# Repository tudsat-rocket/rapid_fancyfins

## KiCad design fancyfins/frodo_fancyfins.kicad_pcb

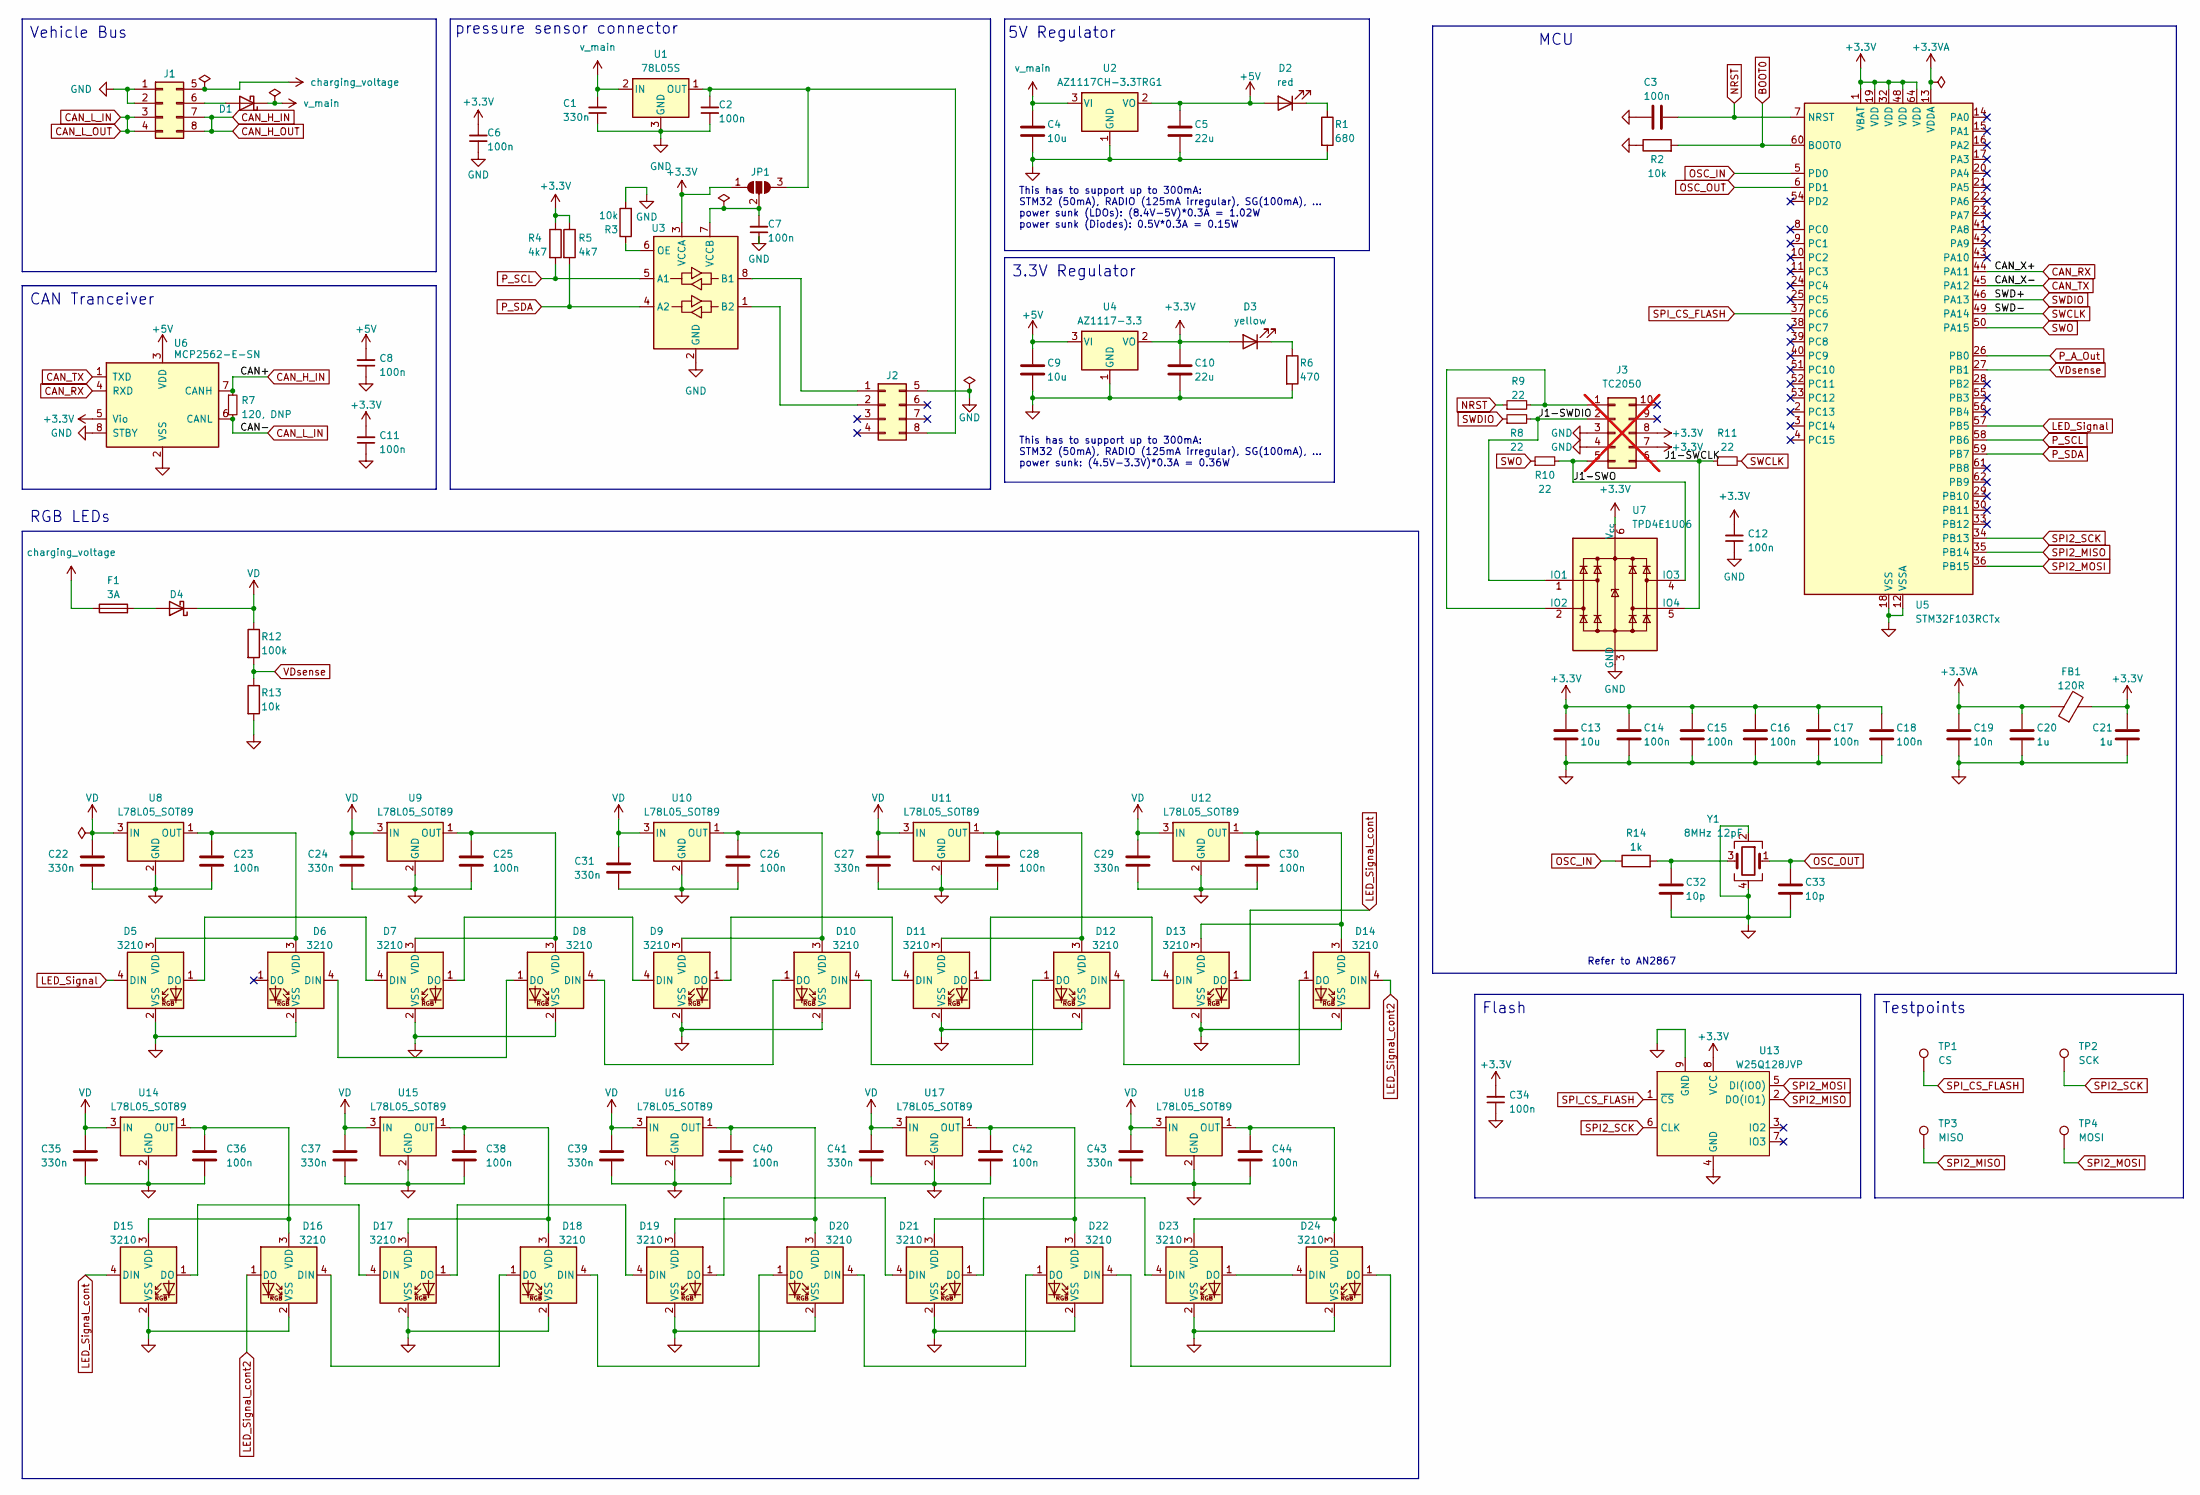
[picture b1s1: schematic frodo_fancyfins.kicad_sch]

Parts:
C1: 330n; C_0402_1005Metric
C2, C6, C7, C12: 100n; C_0402_1005Metric; Part# CL10B104KB8NNNC; LCSC C1525
C3, C8, C11, C14, C15, C16, C17, C18, C34: 100n; C_0402_1005Metric_Pad0.74x0.62mm_HandSolder; LCSC# C307331
C4, C9, C13: 10u; C_0603_1608Metric_Pad1.08x0.95mm_HandSolder; LCSC# C96446
C5, C10: 22u; C_0805_2012Metric_Pad1.18x1.45mm_HandSolder; LCSC# C45783
C19: 10n; C_0402_1005Metric; LCSC# C15195
C20, C21: 1u; C_0402_1005Metric; LCSC# C14445
C22, C24, C27, C29, C31, C35, C37, C39, C41, C43: 330n; C_0402_1005Metric; LCSC# C5448882
C23, C25, C26, C28, C30, C36, C38, C40, C42, C44: 100n; C_0402_1005Metric; LCSC# C1525
C32, C33: 10p; C_0402_1005Metric_Pad0.74x0.62mm_HandSolder; LCSC# C32949
D1: SK34; D_SMA; LCSC # C5140034
D2: red; LED_0603_1608Metric_Pad1.05x0.95mm_HandSolder; LCSC# C2286
D3: yellow; LED_0603_1608Metric_Pad1.05x0.95mm_HandSolder; LCSC# C72038
D4: SK34; D_SMA; LCSC# C5140034
D5, D6, D7, D8, D9, D10, D11, D12, D13, D14, D15, D16, D17, D18, D19, D20, D21, D22, D23, D24: 3210; 1313210530000
F1: 3A; Fuse_1206_3216Metric_Pad1.42x1.75mm_HandSolder
FB1: 120R; L_0402_1005Metric; LCSC# C1002
J1, J2: card_edge_connector_2x4
J3: TC2050; Tag-Connect_TC2050-IDC-FP_2x05_P1.27mm_Vertical; not fitted
JP1: SolderJumper_3_Open; SolderJumper-3_P1.3mm_Open_RoundedPad1.0x1.5mm
R1: 680; R_0603_1608Metric_Pad0.98x0.95mm_HandSolder; LCSC# C23228
R2, R3, R13: 10k; R_0402_1005Metric; LCSC# C25744
R4, R5: 4k7; R_0603_1608Metric
R6: 470; R_0402_1005Metric; LCSC# C25117
R7: 120, DNP; R_0603_1608Metric_Pad0.98x0.95mm_HandSolder
R8, R9, R10, R11: 22; R_0402_1005Metric; Part# RC0603FR-0710KL; LCSC C25092
R12: 100k; R_0402_1005Metric; LCSC# C25741
R14: 1k; R_0402_1005Metric; LCSC# C11702
TP1: CS; TestPoint_Pad_D2.0mm
TP2: SCK; TestPoint_Pad_D2.0mm
TP3: MISO; TestPoint_Pad_D2.0mm
TP4: MOSI; TestPoint_Pad_D2.0mm
U1: 78L05S; SOT-23; LCSC# C2983743
U2: AZ1117CH-3.3TRG1; SOT-223-3_TabPin2; LCSC# C92102
U3: TXB0102DCU; VSSOP-8_2.3x2mm_P0.5mm
U4: AZ1117-3.3; SOT-223-3_TabPin2; LCSC# C110474
U5: STM32F103RCTx; LQFP-64_10x10mm_P0.5mm; LCSC# C8323
U6: MCP2562-E-SN; SOIC-8_3.9x4.9mm_P1.27mm; DigiKey# MCP2562-H/SN
U7: TPD4E1U06; SOT-563; LCSC C527516
U8, U9, U10, U11, U12, U14, U15, U16, U17, U18: L78L05_SOT89; SOT-89-3; LCSC# C42738
U13: W25Q128JVP; WSON-8-1EP_6x5mm_P1.27mm_EP3.4x4.3mm; LCSC# C190862
Y1: 8MHz 12pF; Crystal_SMD_5032-4Pin_5.0x3.2mm; LCSC# C2149245

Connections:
+3.3V: C6.2, C10.1, C11.2, C12.2, C13.1, C14.1, C15.1, C16.1, C17.1, C18.1, C21.1, C34.2, D3.2 (A), FB1.2, J3.7, J3.8, JP1.1 (A), R4.1, R5.1, U3.3 (VCCA), U4.2 (VO), U5.1 (VBAT), U5.19 (VDD), U5.32 (VDD), U5.48 (VDD), U5.64 (VDD), U6.5 (Vio), U7.6 (V_{cc}), U13.8 (VCC)
+3.3VA: C19.1, C20.1, FB1.1, U5.13 (VDDA)
+5V: C5.1, C8.2, C9.1, D2.2 (A), U2.2 (VO), U4.3 (VI), U6.3 (VDD)
/J1-SWCLK: J3.6, R11.1, U7.5 (IO4)
/J1-SWDIO: J3.2, R8.2, U7.1 (IO1)
/J1-SWO: J3.5, R10.2, U7.4 (IO3)
BOOT0: R2.2, U5.60 (BOOT0)
CAN_H_IN: J1.7, J1.8, R7.1, U6.7 (CANH)
CAN_L_IN: J1.3, J1.4, R7.2, U6.6 (CANL)
CAN_RX: U5.44 (PA11), U6.4 (RXD)
CAN_TX: U5.45 (PA12), U6.1 (TXD)
GND: C1.1, C2.1, C3.2, C4.2, C5.2, C6.1, C7.1, C8.1, C9.2, C10.2, C11.1, C12.1, C13.2, C14.2, C15.2, C16.2, C17.2, C18.2, C19.2, C20.2, C21.2, C22.2, C23.2, C24.2, C25.2, C26.2, C27.2, C28.2, C29.2, C30.2, C31.2, C32.2, C33.2, C34.1, C35.2, C36.2, C37.2, C38.2, C39.2, C40.2, C41.2, C42.2, C43.2, C44.2, D5.2 (VSS), D6.2 (VSS), D7.2 (VSS), D8.2 (VSS), D9.2 (VSS), D10.2 (VSS), D11.2 (VSS), D12.2 (VSS), D13.2 (VSS), D14.2 (VSS), D15.2 (VSS), D16.2 (VSS), D17.2 (VSS), D18.2 (VSS), D19.2 (VSS), D20.2 (VSS), D21.2 (VSS), D22.2 (VSS), D23.2 (VSS), D24.2 (VSS), J1.1, J1.2, J2.5, J3.3, J3.4, R1.2, R2.1, R3.2, R6.2, R13.2, U1.3 (GND), U2.1 (GND), U3.2 (GND), U4.1 (GND), U5.12 (VSSA), U5.18 (VSS), U5.31 (VSS), U5.47 (VSS), U5.63 (VSS), U6.2 (VSS), U6.8 (STBY), U7.3 (GND), U8.2 (GND), U9.2 (GND), U10.2 (GND), U11.2 (GND), U12.2 (GND), U13.4 (GND), U13.9 (GND), U14.2 (GND), U15.2 (GND), U16.2 (GND), U17.2 (GND), U18.2 (GND), Y1.2, Y1.4
LED_Signal: D5.4 (DIN), U5.57 (PB5)
LED_Signal_cont: D13.1 (DO), D15.4 (DIN)
LED_Signal_cont2: D14.4 (DIN), D16.1 (DO)
NRST: C3.1, R9.1, U5.7 (NRST)
unnamed: C32.1, R14.2, Y1.3
unnamed: D1.2 (A), J1.6
unnamed: D2.1 (K), R1.1
unnamed: D3.1 (K), R6.1
unnamed: D4.2 (A), F1.2
unnamed: D5.1 (DO), D7.4 (DIN)
unnamed: C23.1, D5.3 (VDD), D6.3 (VDD), U8.1 (OUT)
unnamed: D6.4 (DIN), D8.1 (DO)
unnamed: D7.1 (DO), D9.4 (DIN)
unnamed: C25.1, D7.3 (VDD), D8.3 (VDD), U9.1 (OUT)
unnamed: D10.4 (DIN), D12.1 (DO)
unnamed: D8.4 (DIN), D10.1 (DO)
unnamed: C26.1, D9.3 (VDD), D10.3 (VDD), U10.1 (OUT)
unnamed: D9.1 (DO), D11.4 (DIN)
unnamed: D11.1 (DO), D13.4 (DIN)
unnamed: C28.1, D11.3 (VDD), D12.3 (VDD), U11.1 (OUT)
unnamed: D12.4 (DIN), D14.1 (DO)
unnamed: C30.1, D13.3 (VDD), D14.3 (VDD), U12.1 (OUT)
unnamed: D15.1 (DO), D17.4 (DIN)
unnamed: C36.1, D15.3 (VDD), D16.3 (VDD), U14.1 (OUT)
unnamed: D16.4 (DIN), D18.1 (DO)
unnamed: D17.1 (DO), D19.4 (DIN)
unnamed: C38.1, D17.3 (VDD), D18.3 (VDD), U15.1 (OUT)
unnamed: D18.4 (DIN), D20.1 (DO)
unnamed: D19.1 (DO), D21.4 (DIN)
unnamed: C40.1, D19.3 (VDD), D20.3 (VDD), U16.1 (OUT)
unnamed: D20.4 (DIN), D22.1 (DO)
unnamed: D21.1 (DO), D23.4 (DIN)
unnamed: C42.1, D21.3 (VDD), D22.3 (VDD), U17.1 (OUT)
unnamed: D22.4 (DIN), D24.1 (DO)
unnamed: D23.1 (DO), D24.4 (DIN)
unnamed: C44.1, D23.3 (VDD), D24.3 (VDD), U18.1 (OUT)
unnamed: J2.1, U3.8 (B1)
unnamed: J2.2, U3.1 (B2)
unnamed: C2.2, J2.8, JP1.3 (B), U1.1 (OUT)
unnamed: J3.1, R9.2, U7.2 (IO2)
unnamed: C7.2, JP1.2 (C), U3.7 (VCCB)
unnamed: R3.1, U3.6 (OE)
OSC_IN: R14.1, U5.5 (PD0)
OSC_OUT: C33.1, U5.6 (PD1), Y1.1
P_A_Out: U5.26 (PB0)
P_SCL: R4.2, U3.5 (A1), U5.58 (PB6)
P_SDA: R5.2, U3.4 (A2), U5.59 (PB7)
SPI2_MISO: TP3.1, U5.35 (PB14), U13.2 (DO(IO1))
SPI2_MOSI: TP4.1, U5.36 (PB15), U13.5 (DI(IO0))
SPI2_SCK: TP2.1, U5.34 (PB13), U13.6 (CLK)
SPI_CS_FLASH: TP1.1, U5.37 (PC6), U13.1 (~CS)
SWCLK: R11.2, U5.49 (PA14)
SWDIO: R8.1, U5.46 (PA13)
SWO: R10.1, U5.50 (PA15)
VD: C22.1, C24.1, C27.1, C29.1, C31.1, C35.1, C37.1, C39.1, C41.1, C43.1, D4.1 (K), R12.1, U8.3 (IN), U9.3 (IN), U10.3 (IN), U11.3 (IN), U12.3 (IN), U14.3 (IN), U15.3 (IN), U16.3 (IN), U17.3 (IN), U18.3 (IN)
VDsense: R12.2, R13.1, U5.27 (PB1)
charging_voltage: F1.1, J1.5
v_main: C1.2, C4.1, D1.1 (K), U1.2 (IN), U2.3 (VI)

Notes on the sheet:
This has to support up to 300mA: STM32 (50mA), RADIO (125mA irregular), SG(100mA), ... power sunk (LDOs): (8.4V-5V)*0.3A = 1.02W power sunk (Diodes): 0.5V*0.3A = 0.15W
Vehicle Bus
CAN Tranceiver
Flash
Refer to AN2867
5V Regulator
This has to support up to 300mA: STM32 (50mA), RADIO (125mA irregular), SG(100mA), ... power sunk: (4.5V-3.3V)*0.3A = 0.36W
3.3V Regulator
Testpoints
RGB LEDs
pressure sensor connector
MCU

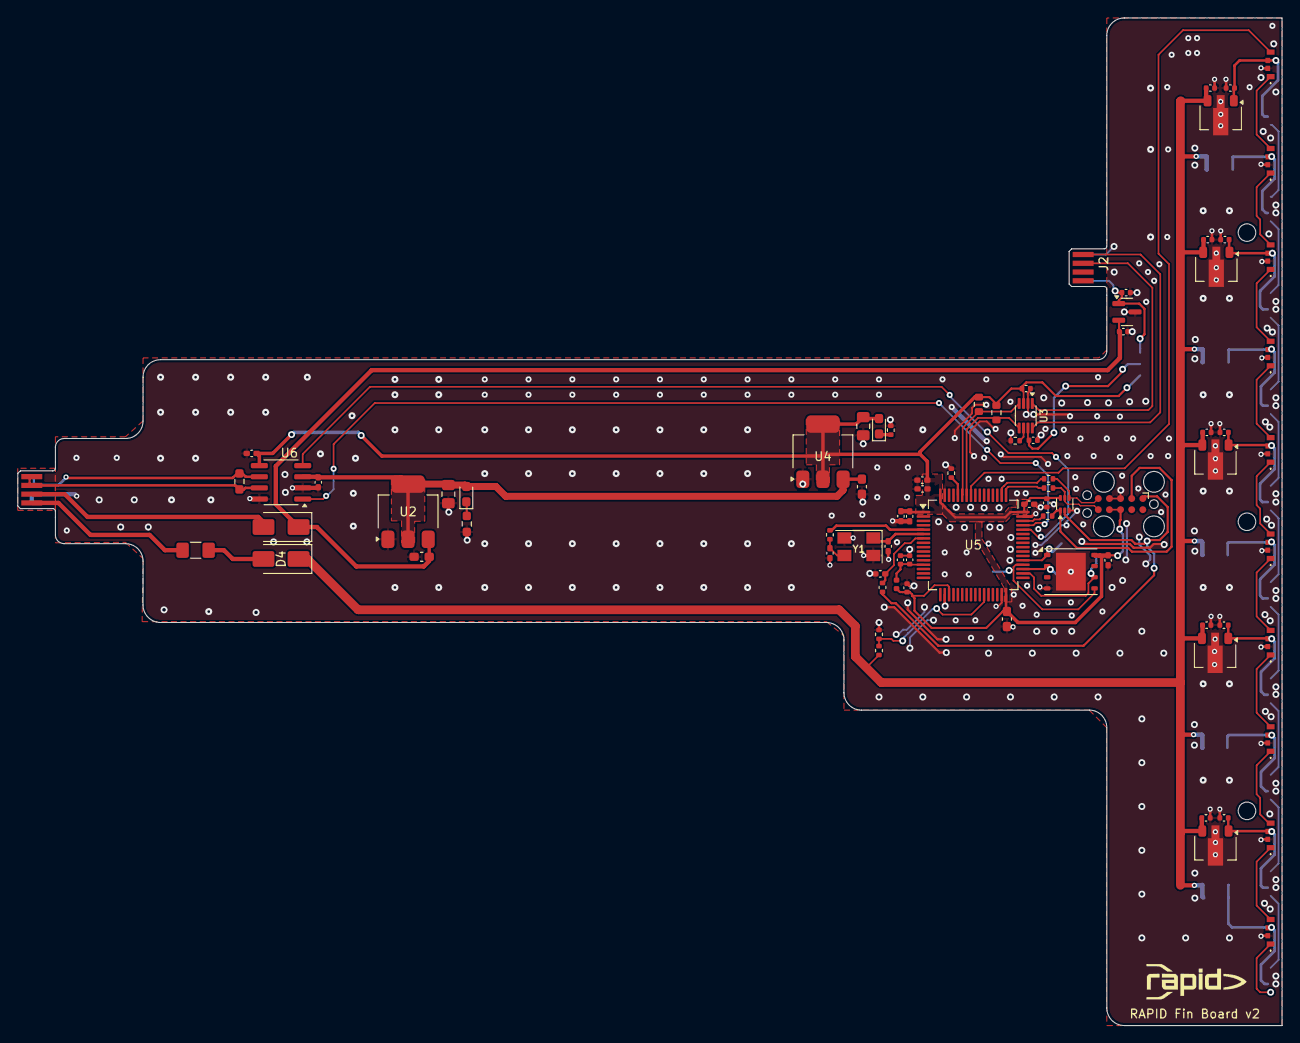
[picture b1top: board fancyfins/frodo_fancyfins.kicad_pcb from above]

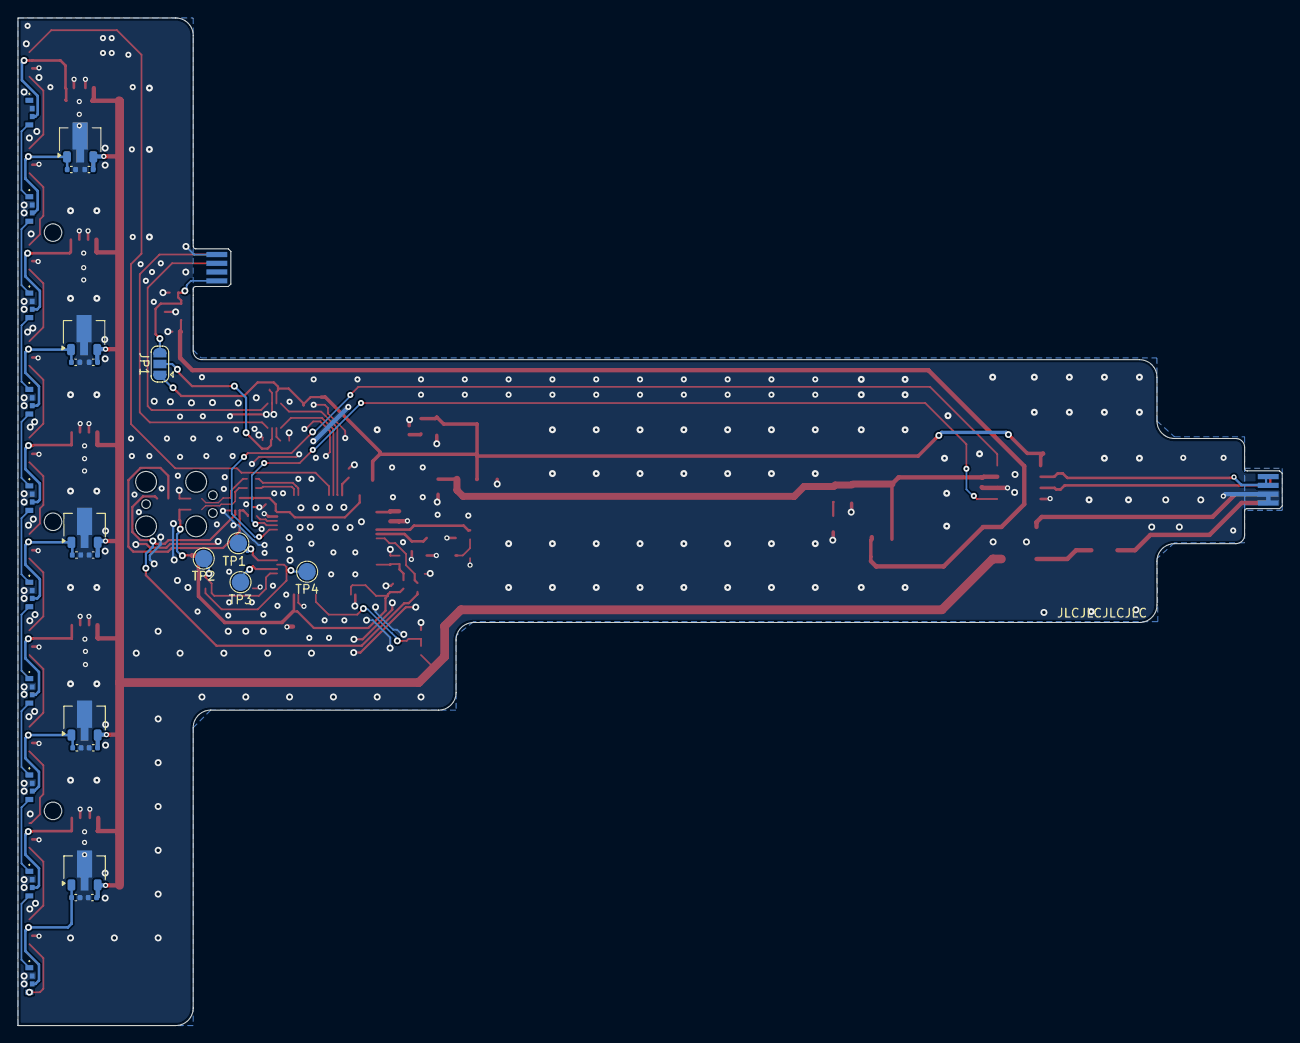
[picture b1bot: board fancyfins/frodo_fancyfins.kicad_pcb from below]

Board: 2 copper layers, 144.3 x 115.0 mm, 111 parts (31 on the bottom side), 69 nets.

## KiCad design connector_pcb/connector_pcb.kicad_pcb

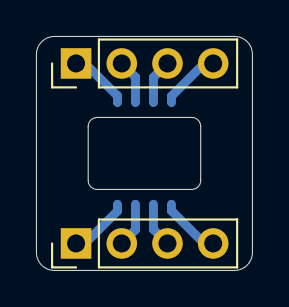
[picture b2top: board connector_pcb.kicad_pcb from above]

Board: 2 copper layers, 12.0 x 13.0 mm, 3 parts (1 on the bottom side), 8 nets.

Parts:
J1: Conn_01x04_Pin; PinHeader_1x04_P2.54mm_Vertical
J2: PinHeader_1x04_P2.54mm_Vertical
J7: Conn_02x04_Top_Bottom; 009159008801906

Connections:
unnamed: J1.1, J7.1
unnamed: J1.2, J7.2
unnamed: J1.3, J7.3
unnamed: J1.4, J7.4
unnamed: J2.1, J7.5
unnamed: J2.2, J7.6
unnamed: J2.3, J7.7
unnamed: J2.4, J7.8

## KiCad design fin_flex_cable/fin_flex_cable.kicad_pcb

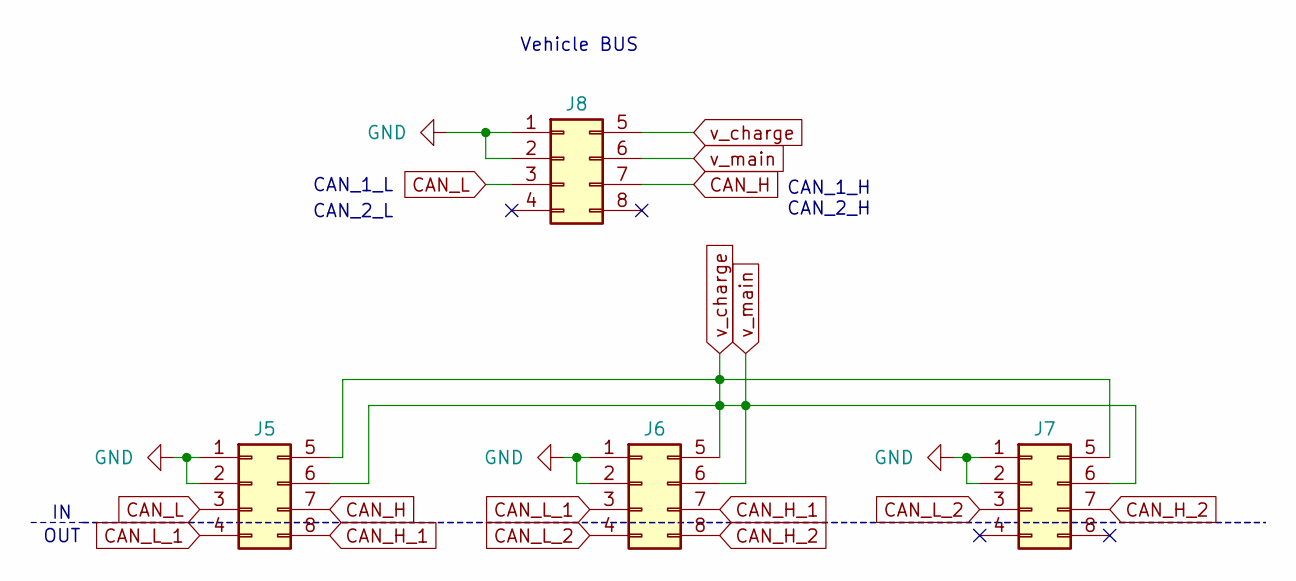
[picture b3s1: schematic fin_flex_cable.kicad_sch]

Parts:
J5, J6, J7: Conn_02x04_Top_Bottom; 009159008801906; Mouser-Nr.: 581-009159008801906
J8: Molex_Micro-Fit_3.0_43045-0800_2x04_P3.00mm_Horizontal

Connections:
CAN_H: J5.7, J8.7
CAN_H_1: J5.8, J6.7
CAN_H_2: J6.8, J7.7
CAN_L: J5.3, J8.3
CAN_L_1: J5.4, J6.3
CAN_L_2: J6.4, J7.3
GND: J5.1, J5.2, J6.1, J6.2, J7.1, J7.2, J8.1, J8.2
v_charge: J5.5, J5.6, J6.5, J6.6, J7.5, J7.6, J8.5, J8.6

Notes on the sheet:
OUT
Vehicle BUS
CAN_1_L
CAN_2_H
CAN_2_L
CAN_1_H

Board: 2 copper layers, 4 parts (0 on the bottom side), 8 nets, no tracks yet.

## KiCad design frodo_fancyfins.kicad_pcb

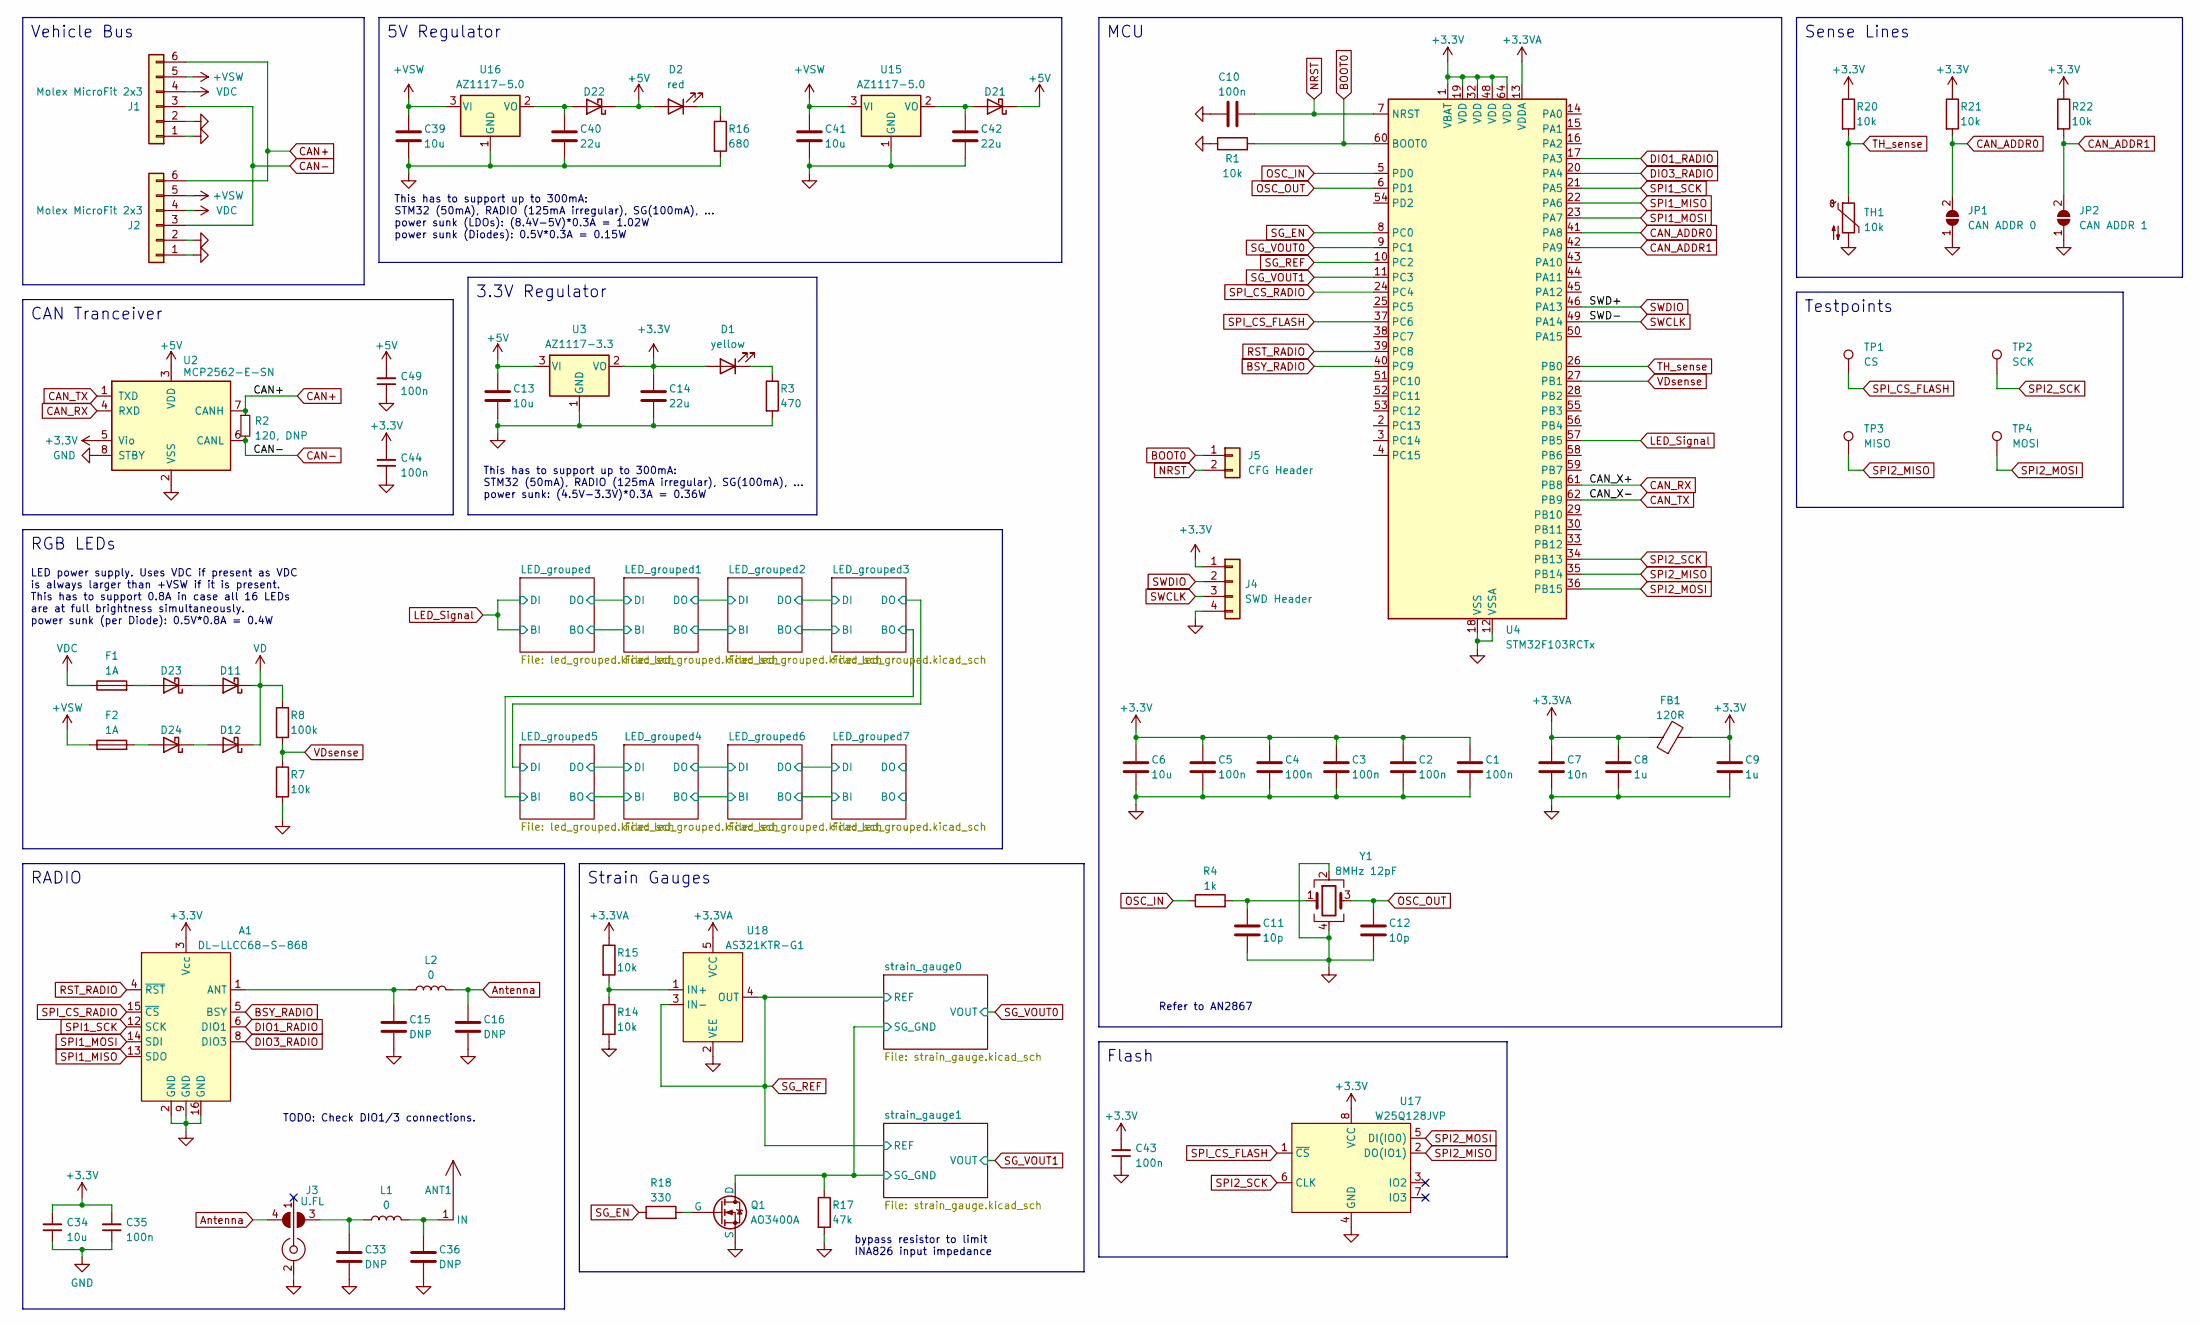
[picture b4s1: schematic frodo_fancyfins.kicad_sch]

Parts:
A1: DL-LLCC68-S-868
ANT1: meandering_monopole_antenna_868MHz
C1, C2, C3, C4, C5, C10, C35, C43, C44, C49: 100n; C_0402_1005Metric_Pad0.74x0.62mm_HandSolder; LCSC# C307331
C6, C13, C34, C39, C41: 10u; C_0603_1608Metric_Pad1.08x0.95mm_HandSolder; LCSC# C96446
C7: 10n; C_0402_1005Metric_Pad0.74x0.62mm_HandSolder; LCSC# C15195
C8, C9: 1u; C_0603_1608Metric_Pad1.08x0.95mm_HandSolder; LCSC# C15849
C11, C12: 10p; C_0402_1005Metric_Pad0.74x0.62mm_HandSolder; LCSC# C32949
C14, C40, C42: 22u; C_0805_2012Metric_Pad1.18x1.45mm_HandSolder; LCSC# C45783
C15, C16, C33, C36: DNP; C_0603_1608Metric_Pad1.08x0.95mm_HandSolder
D1: yellow; LED_0603_1608Metric_Pad1.05x0.95mm_HandSolder; LCSC# C72038
D2: red; LED_0603_1608Metric_Pad1.05x0.95mm_HandSolder; LCSC# C2286
D11, D12, D21, D22, D23, D24: D_Schottky; D_SOD-123F; LCSC# C167645
F1, F2: 1A; Fuse_1206_3216Metric_Pad1.42x1.75mm_HandSolder
FB1: 120R; L_0603_1608Metric_Pad1.05x0.95mm_HandSolder; LCSC# C1002
J1, J2: Molex MicroFit 2x3; Molex_Micro-Fit_3.0_43045-0612_2x03_P3.00mm_Vertical
J3: U.FL; SolderJumper-U.FL
J4: SWD Header; PinHeader_1x04_P2.54mm_Vertical
J5: CFG Header; PinHeader_1x02_P2.54mm_Vertical
JP1: CAN ADDR 0; SolderJumper-2_P1.3mm_Open_RoundedPad1.0x1.5mm
JP2: CAN ADDR 1; SolderJumper-2_P1.3mm_Open_RoundedPad1.0x1.5mm
L1, L2: 0; L_0603_1608Metric_Pad1.05x0.95mm_HandSolder
Q1: AO3400A; SOT-23-3; LCSC# C20917
R1, R7, R14, R15: 10k; R_0402_1005Metric_Pad0.72x0.64mm_HandSolder; LCSC# C25744
R2: 120, DNP; R_0603_1608Metric_Pad0.98x0.95mm_HandSolder
R3: 470; R_0402_1005Metric_Pad0.72x0.64mm_HandSolder; LCSC# C25117
R4: 1k; R_0402_1005Metric_Pad0.72x0.64mm_HandSolder; LCSC# C11702
R8: 100k; R_0402_1005Metric_Pad0.72x0.64mm_HandSolder; LCSC# C25741
R16: 680; R_0603_1608Metric_Pad0.98x0.95mm_HandSolder; LCSC# C23228
R17: 47k; R_0402_1005Metric_Pad0.72x0.64mm_HandSolder; LCSC# C25792
R18: 330; R_0402_1005Metric_Pad0.72x0.64mm_HandSolder; LCSC# C25104
R20, R21, R22: 10k; R_0603_1608Metric_Pad0.98x0.95mm_HandSolder; LCSC# C25804
TH1: 10k; R_0603_1608Metric_Pad0.98x0.95mm_HandSolder; Part# NCP18XH103F03RB; LCSC# C13564
TP1: CS; TestPoint_Pad_D2.0mm
TP2: SCK; TestPoint_Pad_D2.0mm
TP3: MISO; TestPoint_Pad_D2.0mm
TP4: MOSI; TestPoint_Pad_D2.0mm
U2: MCP2562-E-SN; SOIC-8_3.9x4.9mm_P1.27mm; DigiKey# MCP2562-H/SN
U3: AZ1117-3.3; SOT-223-3_TabPin2; LCSC# C110474
U4: STM32F103RCTx; LQFP-64_10x10mm_P0.5mm; LCSC# C8323
U15, U16: AZ1117-5.0; SOT-223-3_TabPin2; LCSC# C526405
U17: W25Q128JVP; WSON-8-1EP_6x5mm_P1.27mm_EP3.4x4.3mm; LCSC# C190862
U18: AS321KTR-G1; SOT25; LCSC# C144156
Y1: 8MHz 12pF; Crystal_SMD_5032-4Pin_5.0x3.2mm; LCSC# C2149245

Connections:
+5V: C13.1, C49.2, D2.2 (A), D21.1 (K), D22.1 (K), U2.3 (VDD), U3.3 (VI)
+VSW: C39.1, C41.1, F2.1, J1.5, J2.5, U15.3 (VI), U16.3 (VI)
/strain_gauge0/SG_GND: Q1.3 (D), R17.1; also elsewhere on the board
Antenna: C16.1, J3.4, L2.2
BOOT0: J5.1, R1.2, U4.60 (BOOT0)
BSY_RADIO: A1.5 (BSY), U4.40 (PC9)
CAN+: J1.6, J2.6, R2.1, U2.7 (CANH)
CAN-: J1.3, J2.3, R2.2, U2.6 (CANL)
CAN_ADDR0: JP1.2 (B), R21.2, U4.41 (PA8)
CAN_ADDR1: JP2.2 (B), R22.2, U4.42 (PA9)
CAN_RX: U2.4 (RXD), U4.61 (PB8)
CAN_TX: U2.1 (TXD), U4.62 (PB9)
DIO1_RADIO: A1.6 (DIO1), U4.17 (PA3)
DIO3_RADIO: A1.8 (DIO3), U4.20 (PA4)
GND: A1.2 (GND), A1.9 (GND), A1.16 (GND), C1.2, C2.2, C3.2, C4.2, C5.2, C6.2, C7.2, C8.2, C9.2, C10.2, C11.2, C12.2, C13.2, C14.2, C15.2, C16.2, C33.2, C34.1, C35.1, C36.2, C39.2, C40.2, C41.2, C42.2, C43.1, C44.1, C49.1, J1.1, J1.2, J2.1, J2.2, J3.2, J4.4, JP1.1 (A), JP2.1 (A), Q1.2 (S), R1.1, R3.2, R7.2, R14.2, R16.2, R17.2, TH1.2, U2.2 (VSS), U2.8 (STBY), U3.1 (GND), U4.12 (VSSA), U4.18 (VSS), U4.31 (VSS), U4.47 (VSS), U4.63 (VSS), U15.1 (GND), U16.1 (GND), U17.4 (GND), U18.2 (VEE), Y1.2, Y1.4; also elsewhere on the board
LED_Signal: U4.57 (PB5); also elsewhere on the board
NRST: C10.1, J5.2, U4.7 (NRST)
unnamed: A1.1 (ANT), C15.1, L2.1
unnamed: ANT1.1 (IN), C36.1, L1.2
unnamed: C11.1, R4.2, Y1.1
unnamed: C33.1, J3.3, L1.1
unnamed: D1.1 (K), R3.1
unnamed: D2.1 (K), R16.1
unnamed: D11.2 (A), D23.1 (K)
unnamed: D12.2 (A), D24.1 (K)
unnamed: C42.1, D21.2 (A), U15.2 (VO)
unnamed: C40.1, D22.2 (A), U16.2 (VO)
unnamed: D23.2 (A), F1.2
unnamed: D24.2 (A), F2.2
unnamed: Q1.1 (G), R18.2
unnamed: R14.1, R15.2, U18.1 (IN+)
OSC_IN: R4.1, U4.5 (PD0)
OSC_OUT: C12.1, U4.6 (PD1), Y1.3
RST_RADIO: A1.4 (~RST), U4.39 (PC8)
SG_EN: R18.1, U4.8 (PC0)
SG_REF: U4.10 (PC2), U18.3 (IN-), U18.4 (OUT); also elsewhere on the board
SG_VOUT0: U4.9 (PC1); also elsewhere on the board
SG_VOUT1: U4.11 (PC3); also elsewhere on the board
SPI1_MISO: A1.13 (SDO), U4.22 (PA6)
SPI1_MOSI: A1.14 (SDI), U4.23 (PA7)
SPI1_SCK: A1.12 (SCK), U4.21 (PA5)
SPI2_MISO: TP3.1, U4.35 (PB14), U17.2 (DO(IO1))
SPI2_MOSI: TP4.1, U4.36 (PB15), U17.5 (DI(IO0))
SPI2_SCK: TP2.1, U4.34 (PB13), U17.6 (CLK)
SPI_CS_FLASH: TP1.1, U4.37 (PC6), U17.1 (~CS)
SPI_CS_RADIO: A1.15 (~CS), U4.24 (PC4)
SWCLK: J4.3, U4.49 (PA14)
SWDIO: J4.2, U4.46 (PA13)
TH_sense: R20.2, TH1.1, U4.26 (PB0)
VD: D11.1 (K), D12.1 (K), R8.1; also elsewhere on the board
VDC: F1.1, J1.4, J2.4
VDsense: R7.1, R8.2, U4.27 (PB1)

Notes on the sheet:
LED power supply. Uses VDC if present as VDC is always larger than +VSW if it is present. This has to support 0.8A in case all 16 LEDs are at full brightness simultaneously. power sunk (per Diode): 0.5V*0.8A = 0.4W
Sense Lines
This has to support up to 300mA: STM32 (50mA), RADIO (125mA irregular), SG(100mA), ... power sunk (LDOs): (8.4V-5V)*0.3A = 1.02W power sunk (Diodes): 0.5V*0.3A = 0.15W
Vehicle Bus
CAN Tranceiver
Flash
Refer to AN2867
5V Regulator
This has to support up to 300mA: STM32 (50mA), RADIO (125mA irregular), SG(100mA), ... power sunk: (4.5V-3.3V)*0.3A = 0.36W
bypass resistor to limit INA826 input impedance
3.3V Regulator
Testpoints
RGB LEDs
RADIO
Strain Gauges
TODO: Check DIO1/3 connections.
MCU

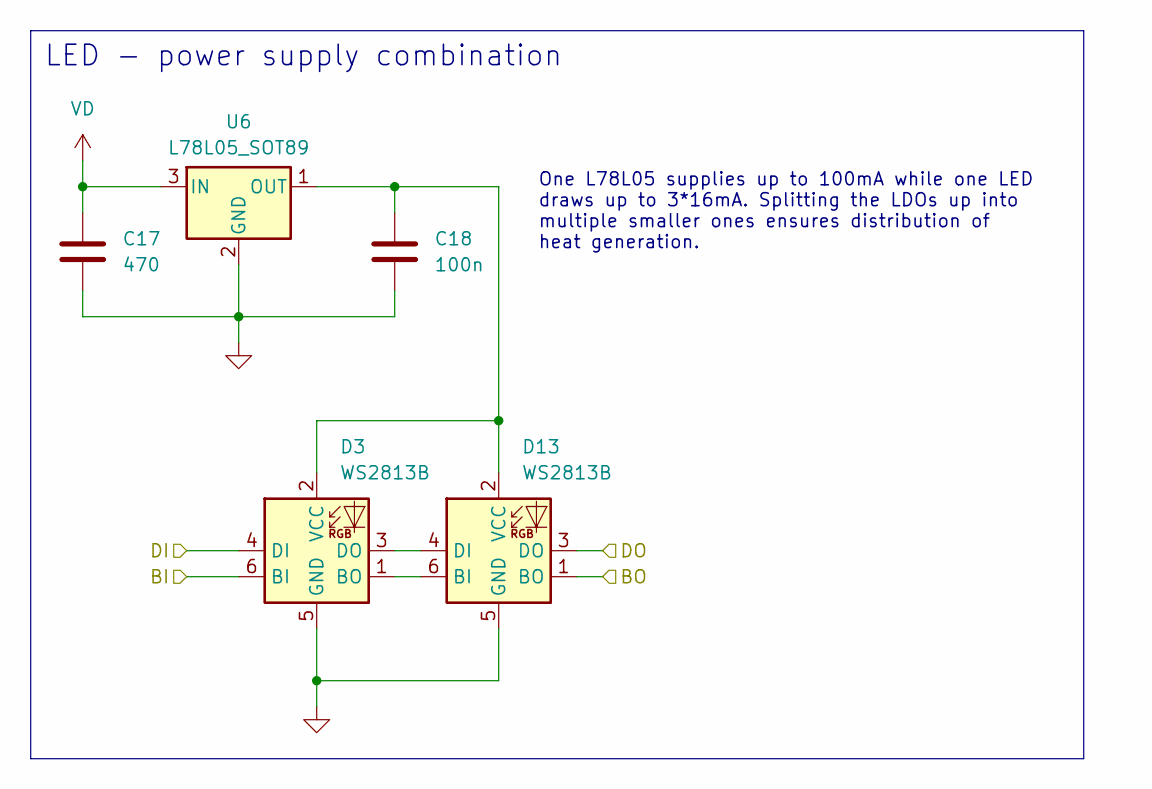
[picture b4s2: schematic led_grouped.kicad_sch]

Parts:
C17: 470; C_0603_1608Metric_Pad1.08x0.95mm_HandSolder; LCSC# C1623
C18: 100n; C_0402_1005Metric_Pad0.74x0.62mm_HandSolder; LCSC# C307331
D3, D13: WS2813B; LED_WS2812_PLCC6_5.0x5.0mm_P1.6mm; LCSC# C965558
U6: L78L05_SOT89; SOT-89-3; LCSC# C42738

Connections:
/LED_grouped/BO: D13.1 (BO); also elsewhere on the board
/LED_grouped/DO: D13.3 (DO); also elsewhere on the board
GND: C17.2, C18.2, D3.5 (GND), D13.5 (GND), U6.2 (GND); also elsewhere on the board
LED_Signal: D3.4 (DI), D3.6 (BI); also elsewhere on the board
unnamed: D3.1 (BO), D13.6 (BI)
unnamed: D3.3 (DO), D13.4 (DI)
unnamed: C18.1, D3.2 (VCC), D13.2 (VCC), U6.1 (OUT)
VD: C17.1, U6.3 (IN); also elsewhere on the board

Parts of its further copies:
C19, C21, C23, C25, C27, C29, C31: 470; C_0603_1608Metric_Pad1.08x0.95mm_HandSolder; LCSC# C1623
C20, C22, C24, C26, C28, C30, C32: 100n; C_0402_1005Metric_Pad0.74x0.62mm_HandSolder; LCSC# C307331
D4, D5, D6, D7, D8, D9, D10, D14, D15, D16, D17, D18, D19, D20: WS2813B; LED_WS2812_PLCC6_5.0x5.0mm_P1.6mm; LCSC# C965558
U5, U7, U8, U9, U10, U11, U12: L78L05_SOT89; SOT-89-3; LCSC# C42738

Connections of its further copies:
/LED_grouped1/BO: D5.6 (BI), D14.1 (BO)
/LED_grouped1/DO: D5.4 (DI), D14.3 (DO)
/LED_grouped2/BO: D6.6 (BI), D15.1 (BO)
/LED_grouped2/DO: D6.4 (DI), D15.3 (DO)
/LED_grouped3/BO: D7.6 (BI), D16.1 (BO)
/LED_grouped3/DO: D7.4 (DI), D16.3 (DO)
/LED_grouped4/BI: D8.6 (BI), D17.1 (BO)
/LED_grouped4/BO: D9.6 (BI), D18.1 (BO)
/LED_grouped4/DI: D8.4 (DI), D17.3 (DO)
/LED_grouped4/DO: D9.4 (DI), D18.3 (DO)
/LED_grouped6/BO: D10.6 (BI), D19.1 (BO)
/LED_grouped6/DO: D10.4 (DI), D19.3 (DO)
/LED_grouped7/BO: D20.1 (BO)
/LED_grouped7/DO: D20.3 (DO)
/LED_grouped/BO: D4.6 (BI); also elsewhere on the board
/LED_grouped/DO: D4.4 (DI); also elsewhere on the board
GND: C19.2, C20.2, C21.2, C22.2, C23.2, C24.2, C25.2, C26.2, C27.2, C28.2, C29.2, C30.2, C31.2, C32.2, D4.5 (GND), D5.5 (GND), D6.5 (GND), D7.5 (GND), D8.5 (GND), D9.5 (GND), D10.5 (GND), D14.5 (GND), D15.5 (GND), D16.5 (GND), D17.5 (GND), D18.5 (GND), D19.5 (GND), D20.5 (GND), U5.2 (GND), U7.2 (GND), U8.2 (GND), U9.2 (GND), U10.2 (GND), U11.2 (GND), U12.2 (GND); also elsewhere on the board
unnamed: D10.1 (BO), D20.6 (BI)
unnamed: D10.3 (DO), D20.4 (DI)
unnamed: C32.1, D10.2 (VCC), D20.2 (VCC), U12.1 (OUT)
unnamed: D4.1 (BO), D14.6 (BI)
unnamed: D4.3 (DO), D14.4 (DI)
unnamed: C20.1, D4.2 (VCC), D14.2 (VCC), U5.1 (OUT)
unnamed: D5.1 (BO), D15.6 (BI)
unnamed: D5.3 (DO), D15.4 (DI)
unnamed: C22.1, D5.2 (VCC), D15.2 (VCC), U7.1 (OUT)
unnamed: D6.1 (BO), D16.6 (BI)
unnamed: D6.3 (DO), D16.4 (DI)
unnamed: C24.1, D6.2 (VCC), D16.2 (VCC), U8.1 (OUT)
unnamed: D7.1 (BO), D17.6 (BI)
unnamed: D7.3 (DO), D17.4 (DI)
unnamed: C26.1, D7.2 (VCC), D17.2 (VCC), U9.1 (OUT)
unnamed: D8.1 (BO), D18.6 (BI)
unnamed: D8.3 (DO), D18.4 (DI)
unnamed: C28.1, D8.2 (VCC), D18.2 (VCC), U10.1 (OUT)
unnamed: D9.1 (BO), D19.6 (BI)
unnamed: D9.3 (DO), D19.4 (DI)
unnamed: C30.1, D9.2 (VCC), D19.2 (VCC), U11.1 (OUT)
VD: C19.1, C21.1, C23.1, C25.1, C27.1, C29.1, C31.1, U5.3 (IN), U7.3 (IN), U8.3 (IN), U9.3 (IN), U10.3 (IN), U11.3 (IN), U12.3 (IN); also elsewhere on the board

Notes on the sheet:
LED - power supply combination
One L78L05 supplies up to 100mA while one LED draws up to 3*16mA. Splitting the LDOs up into multiple smaller ones ensures distribution of heat generation.

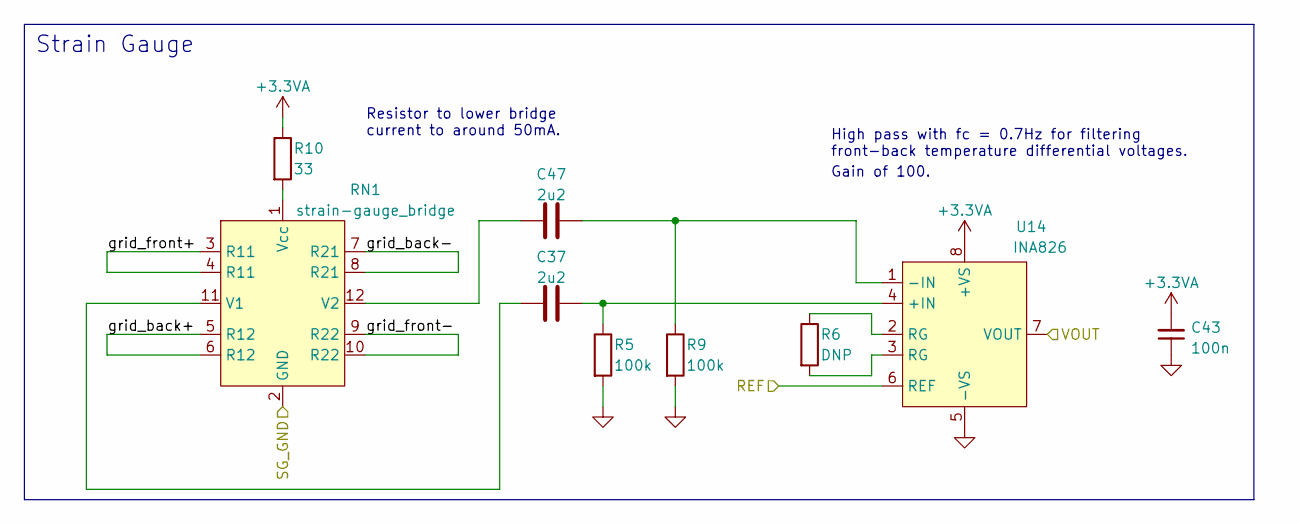
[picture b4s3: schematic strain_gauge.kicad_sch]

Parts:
C37, C47: 2u2; C_0603_1608Metric_Pad1.08x0.95mm_HandSolder; LCSC# C23630
C43: 100n; C_0402_1005Metric_Pad0.74x0.62mm_HandSolder; LCSC# C307331
R5, R9: 100k; R_0402_1005Metric_Pad0.72x0.64mm_HandSolder; LCSC# C25741
R6: DNP; R_0603_1608Metric_Pad0.98x0.95mm_HandSolder
R10: 33; R_0603_1608Metric_Pad0.98x0.95mm_HandSolder; LCSC# C23140
RN1: strain-gauge_bridge
U14: INA826; SOIC-8-1EP_3.9x4.9mm_P1.27mm_EP2.29x3mm; LCSC# C38433

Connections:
/strain_gauge0/SG_GND: RN1.2 (GND); also elsewhere on the board
/strain_gauge0/grid_back+: RN1.5 (R12), RN1.6 (R12)
/strain_gauge0/grid_back-: RN1.7 (R21), RN1.8 (R21)
/strain_gauge0/grid_front+: RN1.3 (R11), RN1.4 (R11)
/strain_gauge0/grid_front-: RN1.9 (R22), RN1.10 (R22)
GND: C43.1, R5.2, R9.2, U14.5 (-VS); also elsewhere on the board
unnamed: R6.1, U14.2 (RG)
unnamed: R6.2, U14.3 (RG)
unnamed: C37.1, RN1.11 (V1)
unnamed: C47.1, RN1.12 (V2)
unnamed: R10.2, RN1.1 (Vcc)
unnamed: C37.2, R5.1, U14.4 (+IN)
unnamed: C47.2, R9.1, U14.1 (-IN)
SG_REF: U14.6 (REF); also elsewhere on the board
SG_VOUT0: U14.7 (VOUT); also elsewhere on the board

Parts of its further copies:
C38, C48: 2u2; C_0603_1608Metric_Pad1.08x0.95mm_HandSolder; LCSC# C23630
C45, C46: 100n; C_0402_1005Metric_Pad0.74x0.62mm_HandSolder; LCSC# C307331
R11: 33; R_0603_1608Metric_Pad0.98x0.95mm_HandSolder; LCSC# C23140
R12, R19: 100k; R_0402_1005Metric_Pad0.72x0.64mm_HandSolder; LCSC# C25741
R13: DNP; R_0603_1608Metric_Pad0.98x0.95mm_HandSolder
RN2: strain-gauge_bridge
U19: INA826; SOIC-8-1EP_3.9x4.9mm_P1.27mm_EP2.29x3mm; LCSC# C38433

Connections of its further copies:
/strain_gauge0/SG_GND: RN2.2 (GND); also elsewhere on the board
/strain_gauge1/grid_back+: RN2.5 (R12), RN2.6 (R12)
/strain_gauge1/grid_back-: RN2.7 (R21), RN2.8 (R21)
/strain_gauge1/grid_front+: RN2.3 (R11), RN2.4 (R11)
/strain_gauge1/grid_front-: RN2.9 (R22), RN2.10 (R22)
GND: C45.1, C46.1, R12.2, R19.2, U19.5 (-VS); also elsewhere on the board
unnamed: R13.1, U19.2 (RG)
unnamed: R13.2, U19.3 (RG)
unnamed: C38.1, RN2.11 (V1)
unnamed: C48.1, RN2.12 (V2)
unnamed: R11.2, RN2.1 (Vcc)
unnamed: C38.2, R19.1, U19.4 (+IN)
unnamed: C48.2, R12.1, U19.1 (-IN)
SG_REF: U19.6 (REF); also elsewhere on the board
SG_VOUT1: U19.7 (VOUT); also elsewhere on the board

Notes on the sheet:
Resistor to lower bridge current to around 50mA.
Strain Gauge
High pass with fc = 0.7Hz for filtering front-back temperature differential voltages.
Gain of 100.

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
